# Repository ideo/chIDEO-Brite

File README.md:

# chIDEO-Brite

Design files for the chIDEO-Brite interactive display

### Status

Peripherals are set up and working! Deeper functionality now needs to be developed. (More details on status items at the top of `brite_fw.c`)

### Building

Install Arduino IDE (which installs necessary avr tools).

Under `Tools > Board:... > Board Manager` search for and install `megaTinyCore`. This will install necessary header files for the attiny402.

Open terminal and change directories to wherever you cloned/downloaded this project

```
cd firmware
make
```

### Flashing

Uses https://github.com/ElTangas/jtag2updi running on an arduino to program. Change `AVRCONFIG` to point to the `avrdude.conf` inside of that the jtag2updi directory that you cloned/downloaded.

Either alias avrdude as the location of avrdude on your machine, change `avrdude` under `flash:` in the makefile to point to the location of avrdude on your machine (likely wherever your Arduino IDE is isntalled), or install avrdude through homebrew.

Change `PORT` in the makefile to the port of your Arduino running jtag2updi (will likely start with `/dev/cu.usbmodem`)

Open terminal and change directories to wherever you cloned/downloaded this project

```
cd firmware
make flash
```

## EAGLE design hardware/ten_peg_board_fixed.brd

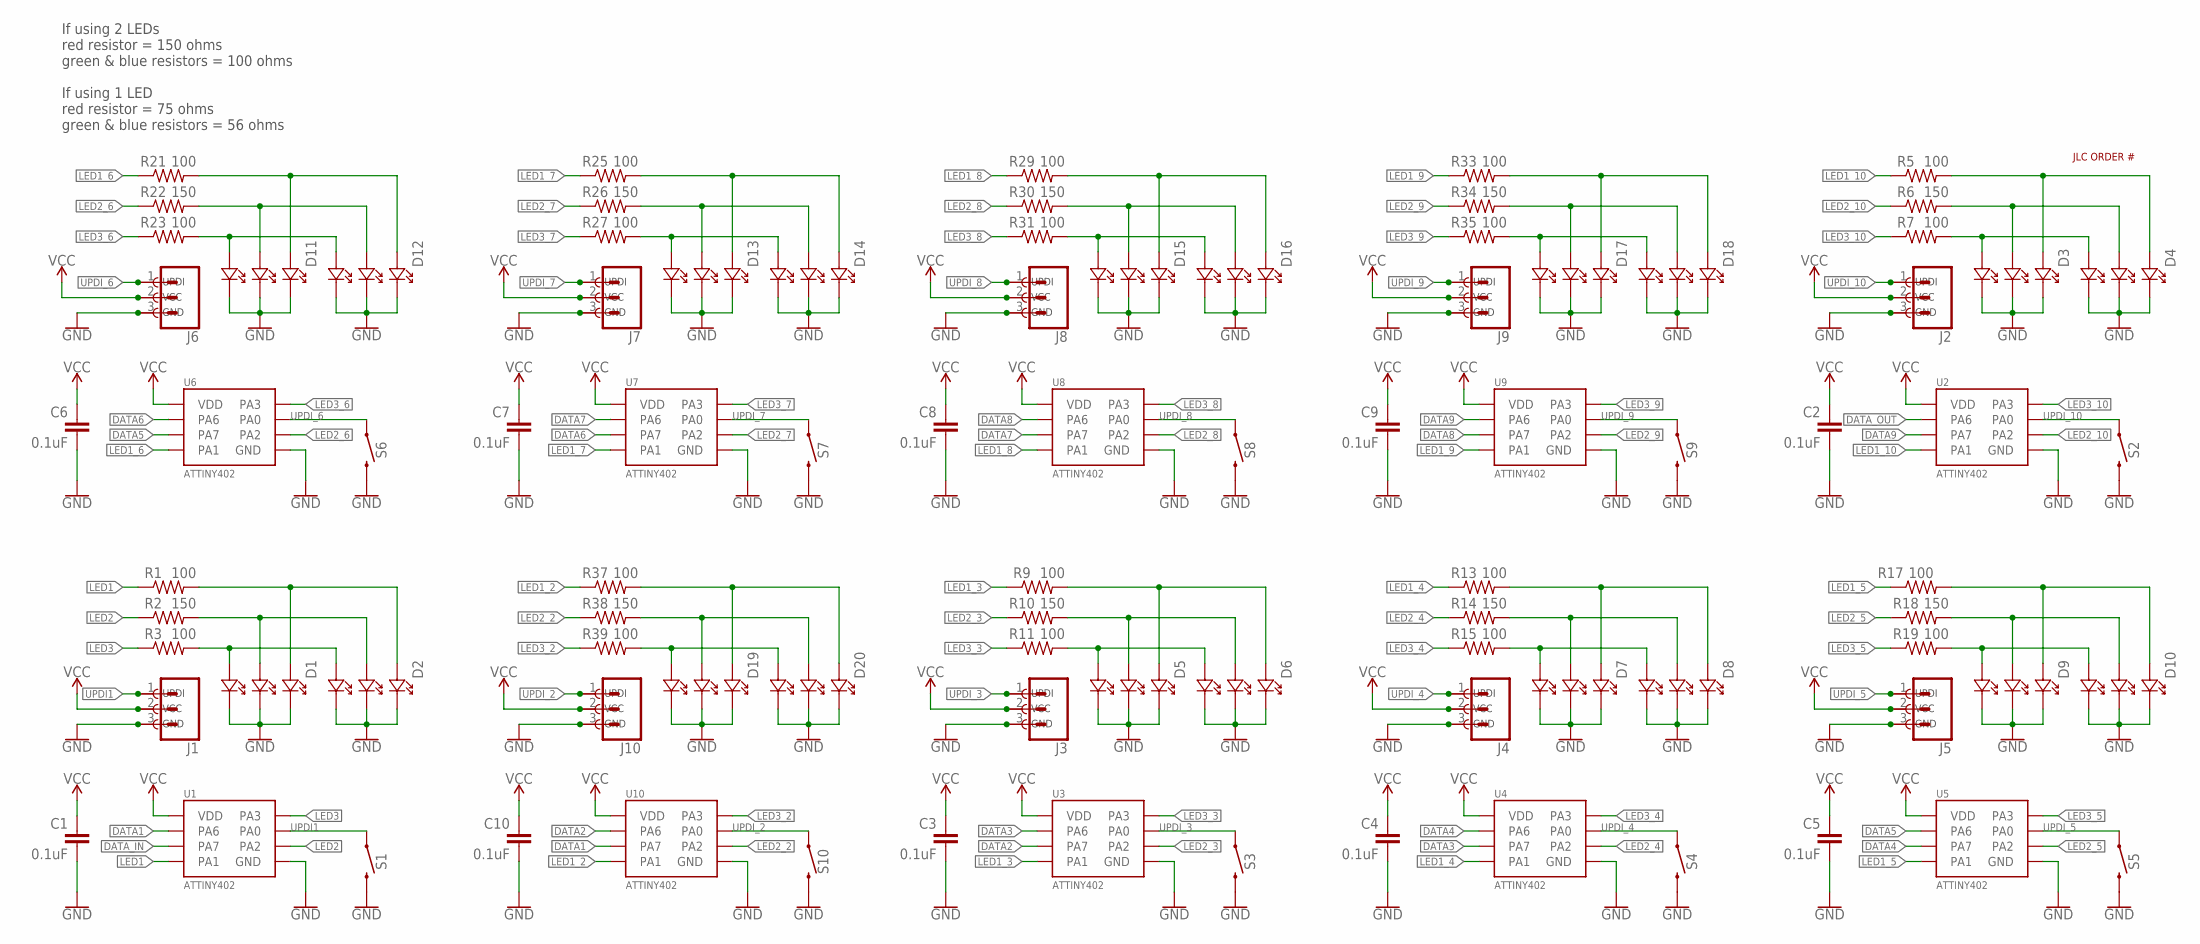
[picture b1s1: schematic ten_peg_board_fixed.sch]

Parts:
C1, C2, C3, C4, C5, C6, C7, C8, C9, C10: 0.1uF; 0603
D1, D2, D3, D4, D5, D6, D7, D8, D9, D10, D11, D12, D13, D14, D15, D16, D17, D18, D19, D20: 19-337C/RSBHGHC-A88/4T; 6-SMD
J1, J2, J3, J4, J5, J6, J7, J8, J9, J10: CONN_03LOCK_LONGPADS; 1X03_LOCK_LONGPADS
R1, R3, R5, R7, R9, R11, R13, R15, R17, R19, R21, R23, R25, R27, R29, R31, R33, R35, R37, R39: 100; 0603
R2, R6, R10, R14, R18, R22, R26, R30, R34, R38: 150; 0603
S1, S2, S3, S4, S5, S6, S7, S8, S9, S10: MOMENTARY-SWITCH-SPST-SMD-4.5MM-WINGED; TACTILE_SWITCH_SMD_4.5MM_WINGED
TP1, TP2, TP3, TP4, TP5, TP6, TP7, TP8, TP9, TP10, TP11, TP12, TP13, TP14, TP15, TP16, TP17, TP18, TP19, TP20, TP21, TP22, TP23, TP24, TP25, TP26, TP27, TP28, TP29, TP30: TEST-POINT3X5; PAD.03X.05
U1, U2, U3, U4, U5, U6, U7, U8, U9, U10: ATTINY402; 8-SOIC
U$1: JLC-ORDER-NUMBER; JLC_ORDER_NUMBER

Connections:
DATA1: U1.P$2 (PA6), U10.P$3 (PA7)
DATA2: U3.P$3 (PA7), U10.P$2 (PA6)
DATA3: U3.P$2 (PA6), U4.P$3 (PA7)
DATA4: U4.P$2 (PA6), U5.P$3 (PA7)
DATA5: U5.P$2 (PA6), U6.P$3 (PA7)
DATA6: U6.P$2 (PA6), U7.P$3 (PA7)
DATA7: U7.P$2 (PA6), U8.P$3 (PA7)
DATA8: U8.P$2 (PA6), U9.P$3 (PA7)
DATA9: U2.P$3 (PA7), U9.P$2 (PA6)
DATA_IN: U1.P$3 (PA7)
DATA_OUT: U2.P$2 (PA6)
GND: C1.2, C2.2, C3.2, C4.2, C5.2, C6.2, C7.2, C8.2, C9.2, C10.2, D1.P$1, D1.P$3, D1.P$5, D2.P$1, D2.P$3, D2.P$5, D3.P$1, D3.P$3, D3.P$5, D4.P$1, D4.P$3, D4.P$5, D5.P$1, D5.P$3, D5.P$5, D6.P$1, D6.P$3, D6.P$5, D7.P$1, D7.P$3, D7.P$5, D8.P$1, D8.P$3, D8.P$5, D9.P$1, D9.P$3, D9.P$5, D10.P$1, D10.P$3, D10.P$5, D11.P$1, D11.P$3, D11.P$5, D12.P$1, D12.P$3, D12.P$5, D13.P$1, D13.P$3, D13.P$5, D14.P$1, D14.P$3, D14.P$5, D15.P$1, D15.P$3, D15.P$5, D16.P$1, D16.P$3, D16.P$5, D17.P$1, D17.P$3, D17.P$5, D18.P$1, D18.P$3, D18.P$5, D19.P$1, D19.P$3, D19.P$5, D20.P$1, D20.P$3, D20.P$5, J1.3, J2.3, J3.3, J4.3, J5.3, J6.3, J7.3, J8.3, J9.3, J10.3, S1.1 (2), S1.4 (2), S2.1 (2), S2.4 (2), S3.1 (2), S3.4 (2), S4.1 (2), S4.4 (2), S5.1 (2), S5.4 (2), S6.1 (2), S6.4 (2), S7.1 (2), S7.4 (2), S8.1 (2), S8.4 (2), S9.1 (2), S9.4 (2), S10.1 (2), S10.4 (2), TP3.P$1, TP6.P$1, TP9.P$1, TP12.P$1, TP15.P$1, TP18.P$1, TP21.P$1, TP24.P$1, TP27.P$1, TP30.P$1, U1.P$8 (GND), U2.P$8 (GND), U3.P$8 (GND), U4.P$8 (GND), U5.P$8 (GND), U6.P$8 (GND), U7.P$8 (GND), U8.P$8 (GND), U9.P$8 (GND), U10.P$8 (GND)
LED1: R1.1, U1.P$4 (PA1)
LED1_2: R37.1, U10.P$4 (PA1)
LED1_3: R9.1, U3.P$4 (PA1)
LED1_4: R13.1, U4.P$4 (PA1)
LED1_5: R17.1, U5.P$4 (PA1)
LED1_6: R21.1, U6.P$4 (PA1)
LED1_7: R25.1, U7.P$4 (PA1)
LED1_8: R29.1, U8.P$4 (PA1)
LED1_9: R33.1, U9.P$4 (PA1)
LED1_10: R5.1, U2.P$4 (PA1)
LED2: R2.1, U1.P$5 (PA2)
LED2_2: R38.1, U10.P$5 (PA2)
LED2_3: R10.1, U3.P$5 (PA2)
LED2_4: R14.1, U4.P$5 (PA2)
LED2_5: R18.1, U5.P$5 (PA2)
LED2_6: R22.1, U6.P$5 (PA2)
LED2_7: R26.1, U7.P$5 (PA2)
LED2_8: R30.1, U8.P$5 (PA2)
LED2_9: R34.1, U9.P$5 (PA2)
LED2_10: R6.1, U2.P$5 (PA2)
LED3: R3.1, U1.P$7 (PA3)
LED3_2: R39.1, U10.P$7 (PA3)
LED3_3: R11.1, U3.P$7 (PA3)
LED3_4: R15.1, U4.P$7 (PA3)
LED3_5: R19.1, U5.P$7 (PA3)
LED3_6: R23.1, U6.P$7 (PA3)
LED3_7: R27.1, U7.P$7 (PA3)
LED3_8: R31.1, U8.P$7 (PA3)
LED3_9: R35.1, U9.P$7 (PA3)
LED3_10: R7.1, U2.P$7 (PA3)
unnamed: D3.P$6, D4.P$6, R7.2
unnamed: D3.P$4, D4.P$4, R6.2
unnamed: D3.P$2, D4.P$2, R5.2
unnamed: D5.P$6, D6.P$6, R11.2
unnamed: D5.P$4, D6.P$4, R10.2
unnamed: D5.P$2, D6.P$2, R9.2
unnamed: D7.P$6, D8.P$6, R15.2
unnamed: D7.P$4, D8.P$4, R14.2
unnamed: D7.P$2, D8.P$2, R13.2
unnamed: D9.P$6, D10.P$6, R19.2
unnamed: D9.P$4, D10.P$4, R18.2
unnamed: D9.P$2, D10.P$2, R17.2
unnamed: D1.P$6, D2.P$6, R3.2
unnamed: D1.P$4, D2.P$4, R2.2
unnamed: D1.P$2, D2.P$2, R1.2
unnamed: D11.P$6, D12.P$6, R23.2
unnamed: D11.P$4, D12.P$4, R22.2
unnamed: D11.P$2, D12.P$2, R21.2
unnamed: D13.P$6, D14.P$6, R27.2
unnamed: D13.P$4, D14.P$4, R26.2
unnamed: D13.P$2, D14.P$2, R25.2
unnamed: D15.P$6, D16.P$6, R31.2
unnamed: D15.P$4, D16.P$4, R30.2
unnamed: D15.P$2, D16.P$2, R29.2
unnamed: D17.P$6, D18.P$6, R35.2
unnamed: D17.P$4, D18.P$4, R34.2
unnamed: D17.P$2, D18.P$2, R33.2
unnamed: D19.P$6, D20.P$6, R39.2
unnamed: D19.P$4, D20.P$4, R38.2
unnamed: D19.P$2, D20.P$2, R37.2
UPDI1: J1.1, S1.2 (1), S1.3 (1), TP25.P$1, U1.P$6 (PA0)
UPDI_2: J10.1, S10.2 (1), S10.3 (1), TP22.P$1, U10.P$6 (PA0)
UPDI_3: J3.1, S3.2 (1), S3.3 (1), TP19.P$1, U3.P$6 (PA0)
UPDI_4: J4.1, S4.2 (1), S4.3 (1), TP16.P$1, U4.P$6 (PA0)
UPDI_5: J5.1, S5.2 (1), S5.3 (1), TP13.P$1, U5.P$6 (PA0)
UPDI_6: J6.1, S6.2 (1), S6.3 (1), TP10.P$1, U6.P$6 (PA0)
UPDI_7: J7.1, S7.2 (1), S7.3 (1), TP7.P$1, U7.P$6 (PA0)
UPDI_8: J8.1, S8.2 (1), S8.3 (1), TP4.P$1, U8.P$6 (PA0)
UPDI_9: J9.1, S9.2 (1), S9.3 (1), TP28.P$1, U9.P$6 (PA0)
UPDI_10: J2.1, S2.2 (1), S2.3 (1), TP1.P$1, U2.P$6 (PA0)
VCC: C1.1, C2.1, C3.1, C4.1, C5.1, C6.1, C7.1, C8.1, C9.1, C10.1, J1.2, J2.2, J3.2, J4.2, J5.2, J6.2, J7.2, J8.2, J9.2, J10.2, TP2.P$1, TP5.P$1, TP8.P$1, TP11.P$1, TP14.P$1, TP17.P$1, TP20.P$1, TP23.P$1, TP26.P$1, TP29.P$1, U1.P$1 (VDD), U2.P$1 (VDD), U3.P$1 (VDD), U4.P$1 (VDD), U5.P$1 (VDD), U6.P$1 (VDD), U7.P$1 (VDD), U8.P$1 (VDD), U9.P$1 (VDD), U10.P$1 (VDD)

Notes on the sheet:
UPDI
VCC
GND
If using 2 LEDs red resistor = 150 ohms green & blue resistors = 100 ohms If using 1 LED red resistor = 75 ohms green & blue resistors = 56 ohms

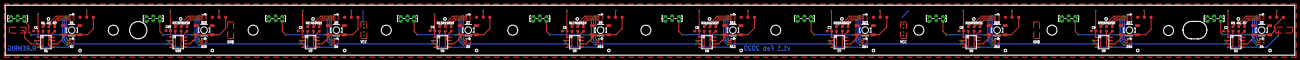
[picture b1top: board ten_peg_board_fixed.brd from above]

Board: 2 copper layers, 492.0 x 19.1 mm, 121 parts (1 on the bottom side), 81 nets.

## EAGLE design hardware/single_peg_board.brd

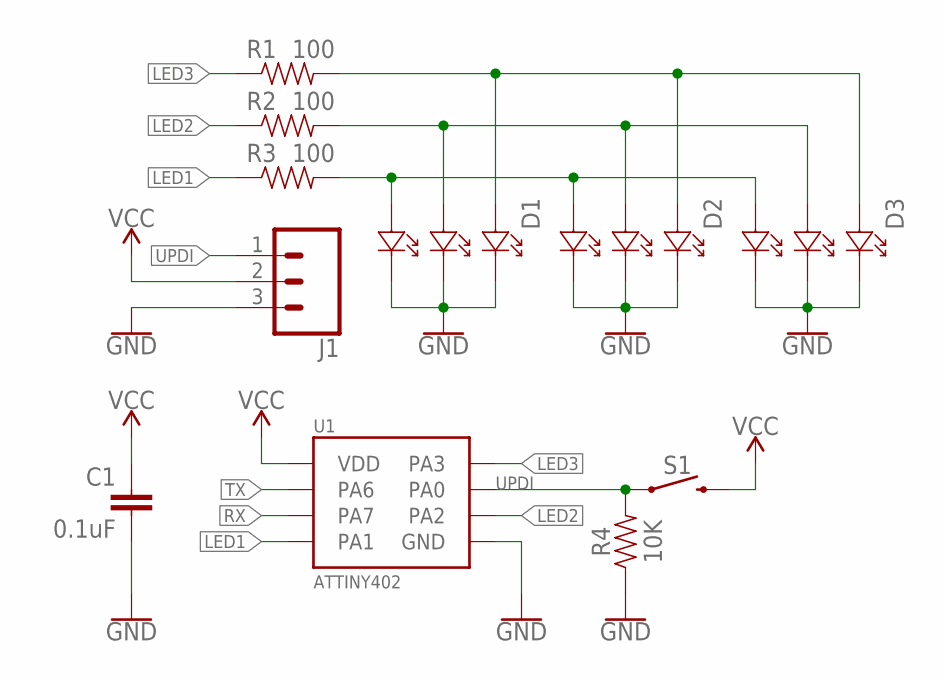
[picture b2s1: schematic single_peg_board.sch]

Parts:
C1: 0.1uF; 0603
D1, D2, D3: 19-337C/RSBHGHC-A88/4T; 6-SMD
J1: CONN_03LONGPADS; 1X03_LONGPADS
R1, R2, R3: 100; 0603
R4: 10K; 0603
S1: MOMENTARY-SWITCH-SPST-SMD-4.5MM-WINGED; TACTILE_SWITCH_SMD_4.5MM_WINGED
U1: ATTINY402; 8-SOIC

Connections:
GND: C1.2, D1.P$1, D1.P$3, D1.P$5, D2.P$1, D2.P$3, D2.P$5, D3.P$1, D3.P$3, D3.P$5, J1.3, R4.1, U1.P$8 (GND)
LED1: R3.1, U1.P$4 (PA1)
LED2: R2.1, U1.P$5 (PA2)
LED3: R1.1, U1.P$7 (PA3)
unnamed: D1.P$6, D2.P$6, D3.P$6, R3.2
unnamed: D1.P$4, D2.P$4, D3.P$4, R2.2
unnamed: D1.P$2, D2.P$2, D3.P$2, R1.2
RX: U1.P$3 (PA7)
TX: U1.P$2 (PA6)
UPDI: J1.1, R4.2, S1.2 (1), S1.3 (1), U1.P$6 (PA0)
VCC: C1.1, J1.2, S1.1 (2), S1.4 (2), U1.P$1 (VDD)

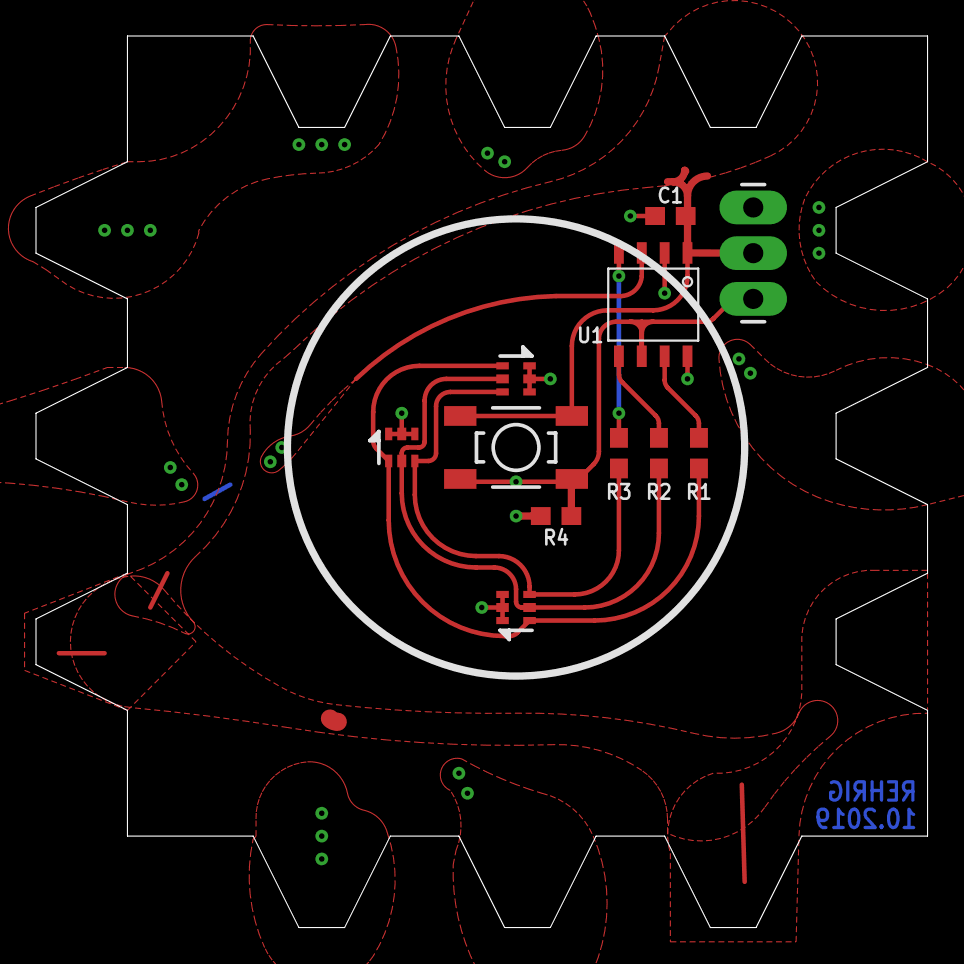
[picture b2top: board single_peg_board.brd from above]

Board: 2 copper layers, 49.5 x 49.5 mm, 11 parts (0 on the bottom side), 9 nets.

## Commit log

2019-10-16 initial commit - basic functionality
2019-10-17 add interrupts
2019-10-18 add save/load to/from memory slot serial command
2020-03-11 add newest board layouts
2020-03-11 add wait period before saving to eeprom for temp values
2020-04-14 Minor fix on line 28
2020-10-31 add color picker and add more comments

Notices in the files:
parts and their libraries:
SparkFun-Capacitors: Licensing: Creative Commons ShareAlike 4.0 International - https://creativecommons.org/licenses/by-sa/4.0
